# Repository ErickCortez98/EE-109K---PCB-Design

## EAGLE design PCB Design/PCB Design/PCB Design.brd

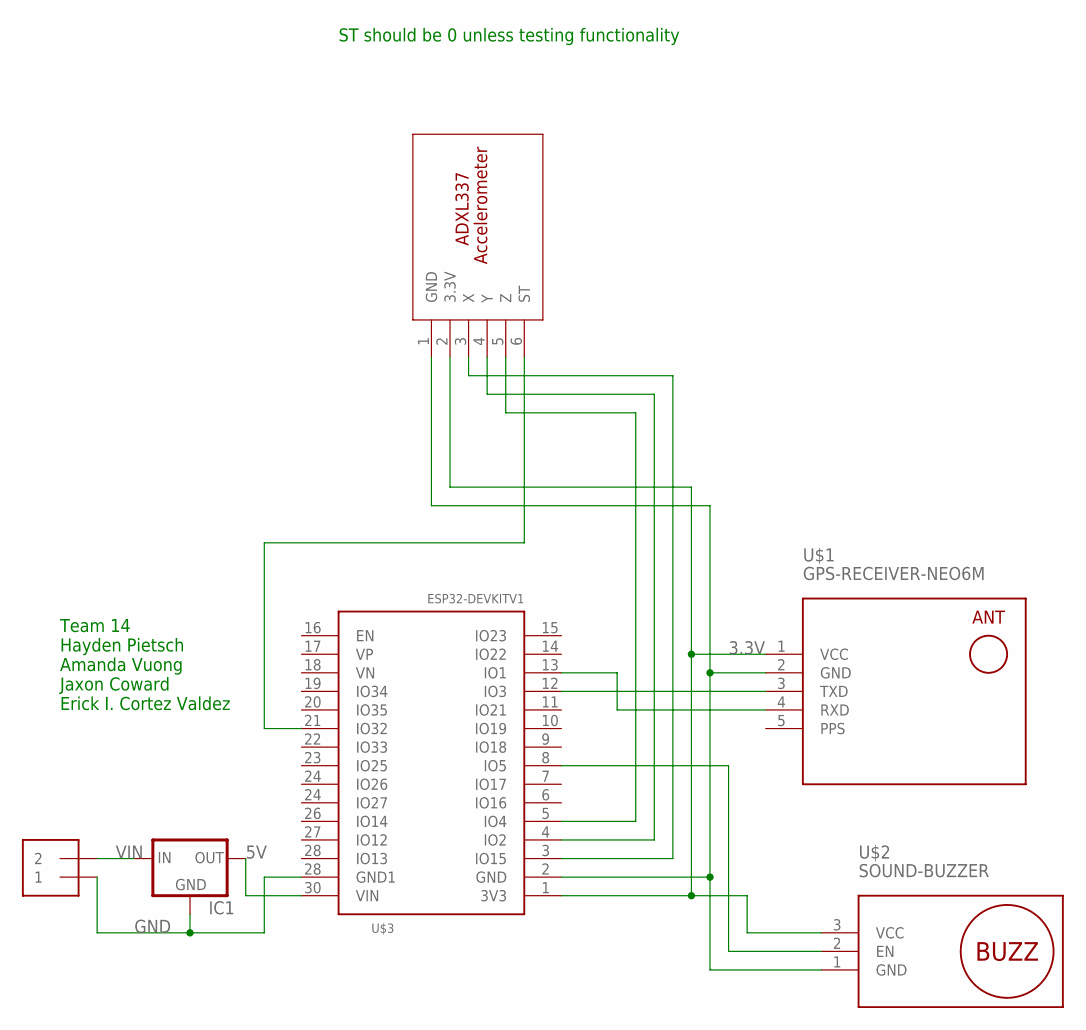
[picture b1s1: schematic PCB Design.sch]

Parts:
IC1: V_REG_78XXSIDE; 78XXL; MPN L7805ABV
J1: 1X2-3.5MM
U$1: GPS-RECEIVER-NEO6M; MPN YR1B909KCC
U$2: SOUND-BUZZER
U$3: ESP32DEVKITV1; ESP32-DEVKITV1
U$4: ADXL337_ACCELEROMETER; ADXL337BREAKOUT

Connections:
3.3V: U$1.1 (VCC), U$2.3 (VCC), U$3.1 (3V3), U$4.2 (3.3V)
5V: IC1.OUT, U$3.30 (VIN)
GND: IC1.GND, J1.1, U$1.2 (GND), U$2.1 (GND), U$3.2 (GND), U$3.28 (IO13), U$4.1 (GND)
unnamed: U$3.21 (IO32), U$4.6 (ST)
unnamed: U$3.3 (IO15), U$4.3 (X)
unnamed: U$3.4 (IO2), U$4.4 (Y)
unnamed: U$3.5 (IO4), U$4.5 (Z)
unnamed: U$1.4 (RXD), U$3.13 (IO1)
unnamed: U$1.3 (TXD), U$3.12 (IO3)
unnamed: U$2.2 (EN), U$3.8 (IO5)
PPS: U$1.5 (PPS)
VIN: IC1.IN, J1.2

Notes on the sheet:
ST should be 0 unless testing functionality
Team 14 Hayden Pietsch Amanda Vuong Jaxon Coward Erick I. Cortez Valdez

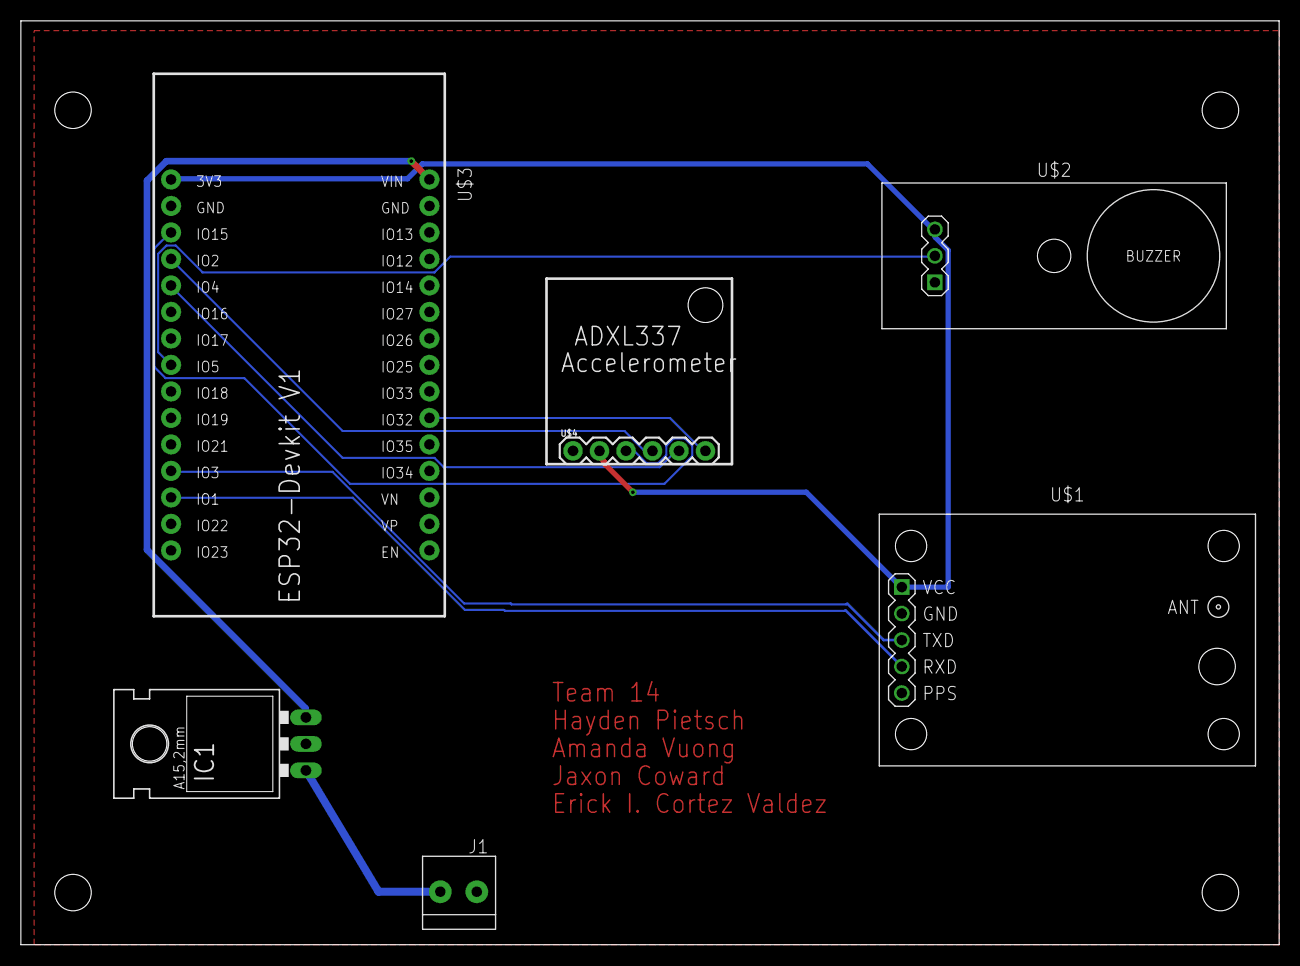
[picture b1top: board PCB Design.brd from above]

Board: 2 copper layers, 120.6 x 88.6 mm, 6 parts (0 on the bottom side), 11 nets.

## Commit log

2020-04-14 added bill of materials excel file
2020-04-14 added eagle schematic file
2020-04-15 Add files via upload
    library with tons of modules
    GPS name is GPS-RECEIVER-NEO6M
2020-04-16 Added Accellerometer and sparkfun sensor library
2020-04-19 Completed Schematic, no text module
2020-04-19 Added 5V regulator and board layout
2020-04-24 added team members names and connection points with labels
2020-04-24 Minor edits to resolve DRC checking
2020-05-08 Fixed Scematic and Board Based on Shawn's suggestions
2020-05-08 3D Models of Components
2020-05-08 Create BOM.xlsx
    Updated Bill of Materials
2020-05-09 CAD desings
2020-05-09 Final zips

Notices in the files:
parts and their libraries:
diy-modules: Released under the Creative Commons Attribution 4.0 International License: http://creativecommons.org/licenses/by/4.0
